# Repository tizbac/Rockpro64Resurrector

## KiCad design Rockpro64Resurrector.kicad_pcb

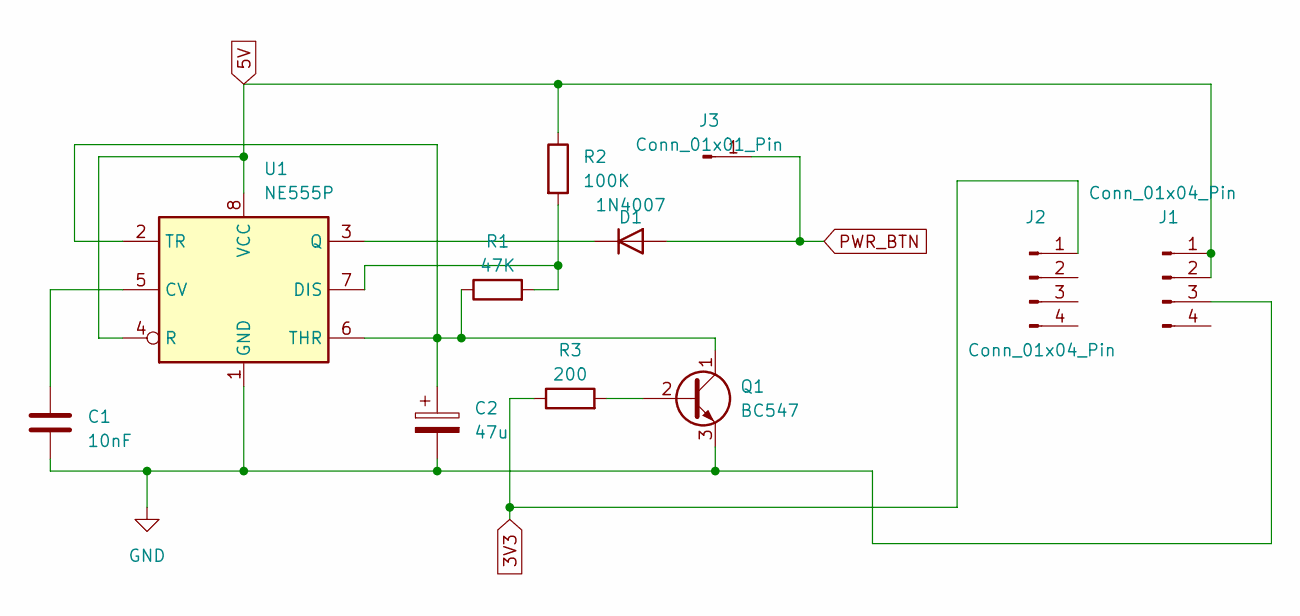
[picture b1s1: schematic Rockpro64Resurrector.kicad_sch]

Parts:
C1: 10nF; C_Rect_L7.2mm_W3.5mm_P5.00mm_FKS2_FKP2_MKS2_MKP2
C2: 47u; CP_Radial_D6.3mm_P2.50mm
D1: 1N4007; D_DO-41_SOD81_P10.16mm_Horizontal
J1, J2: Conn_01x04_Pin; PinHeader_1x04_P2.54mm_Vertical
J3: Conn_01x01_Pin; PinHeader_1x01_P2.54mm_Horizontal
Q1: BC547; TO-92_Inline
R1: 47K; R_Axial_DIN0207_L6.3mm_D2.5mm_P10.16mm_Horizontal
R2: 100K; R_Axial_DIN0207_L6.3mm_D2.5mm_P10.16mm_Horizontal
R3: 200; R_Axial_DIN0207_L6.3mm_D2.5mm_P10.16mm_Horizontal
U1: NE555P; DIP-8_W7.62mm

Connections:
3V3: J2.1, R3.1
5V: J1.1, J1.2, R2.1, U1.4 (R), U1.8 (VCC)
GND: C1.2, C2.2, J1.3, Q1.3 (E), U1.1 (GND)
unnamed: D1.1 (K), U1.3 (Q)
unnamed: Q1.2 (B), R3.2
unnamed: C2.1, Q1.1 (C), R1.1, U1.2 (TR), U1.6 (THR)
unnamed: C1.1, U1.5 (CV)
unnamed: R1.2, R2.2, U1.7 (DIS)
PWR_BTN: D1.2 (A), J3.1

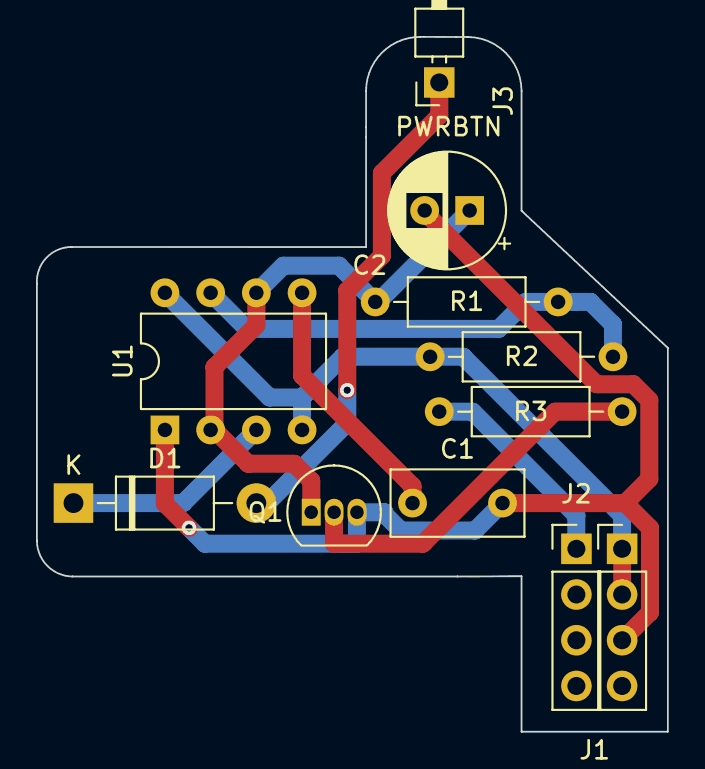
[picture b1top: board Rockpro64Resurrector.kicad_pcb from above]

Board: 2 copper layers, 35.1 x 38.6 mm, 11 parts (0 on the bottom side), 9 nets.

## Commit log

2023-05-11 Added PDF schematic
